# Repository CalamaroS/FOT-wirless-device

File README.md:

# FOT-wirless-device
Master thesis project: Development of a wireless device for lung function assessment in horses.

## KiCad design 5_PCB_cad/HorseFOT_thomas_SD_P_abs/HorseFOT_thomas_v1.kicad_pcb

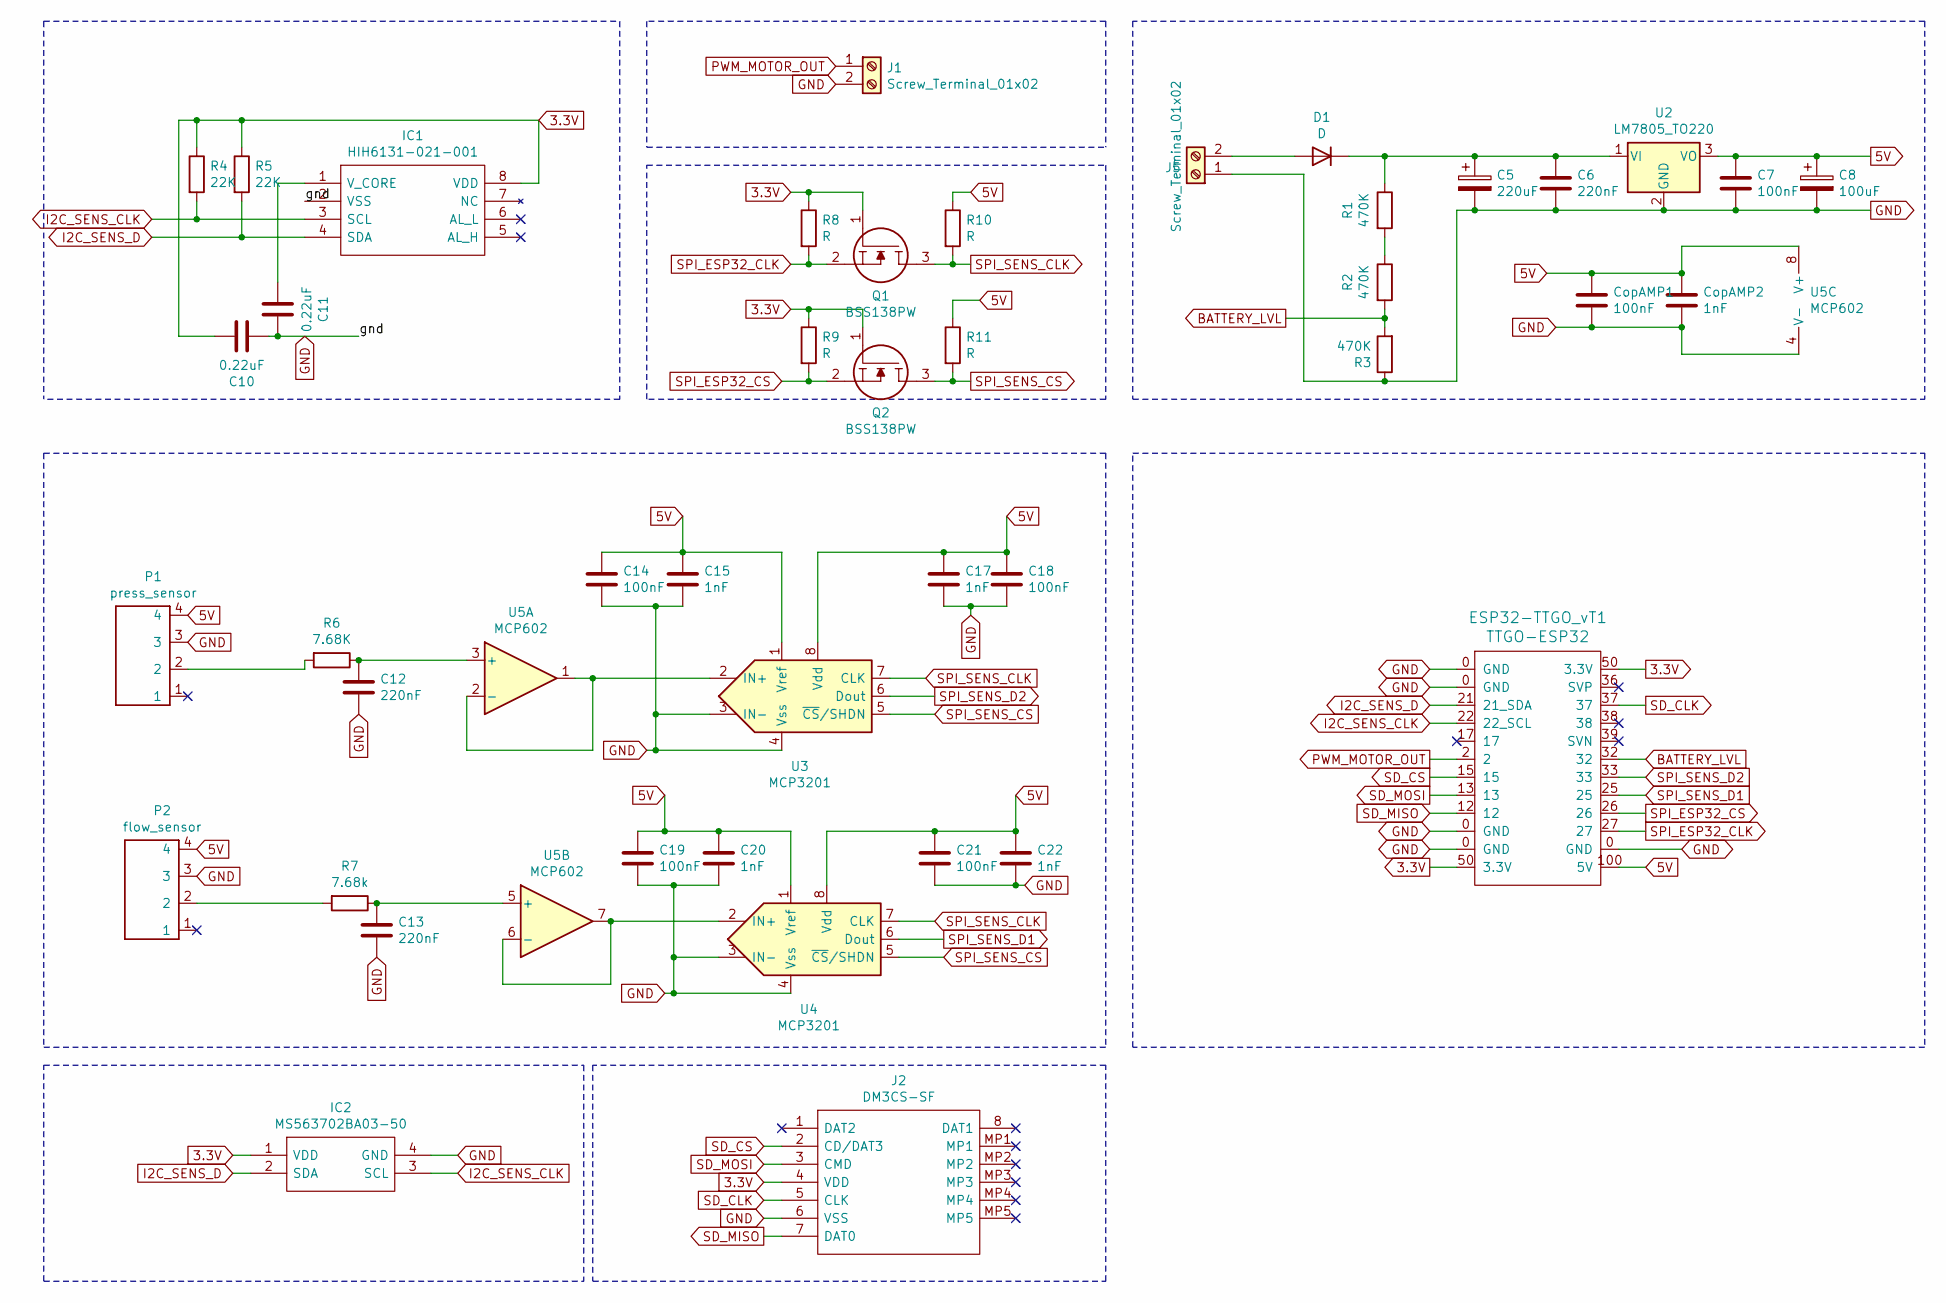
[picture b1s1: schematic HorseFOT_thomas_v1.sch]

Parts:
C5: 220uF; EEE1AA221P
C6, C12, C13: 220nF; C_1206_3216Metric_Pad1.33x1.80mm_HandSolder
C7, C14, C18, C19, C21: 100nF; C_1206_3216Metric_Pad1.33x1.80mm_HandSolder
C8: 100uF; EEE1AA221P
C10, C11: 0.22uF; C_1206_3216Metric_Pad1.33x1.80mm_HandSolder
C15, C17, C20, C22: 1nF; C_1206_3216Metric_Pad1.33x1.80mm_HandSolder
CopAMP1: 100nF; C_1206_3216Metric_Pad1.33x1.80mm_HandSolder
CopAMP2: 1nF; C_1206_3216Metric_Pad1.33x1.80mm_HandSolder
D1: D; D_1206_3216Metric
ESP32-TTGO_vT1: TTGO-ESP32; ESP32-TTGO_vT
IC1: HIH6131-021-001; HIH6131021001; Manufacturer_Part_Number HIH6131-021-001
IC2: MS563702BA03-50; MS5637_1; Manufacturer_Part_Number MS563702BA03-50; Mouser Part Number 824-MS563702BA03-50
J1, J5: Screw_Terminal_01x02; TerminalBlock_bornier-2_P5.08mm
J2: DM3CS-SF; Manufacturer_Part_Number DM3CS-SF; Mouser Part Number 798-DM3CSSF
P1: press_sensor; ELVR-L01D-pressure_sensor
P2: flow_sensor; ELVR-L01D-pressure_sensor
Q1, Q2: BSS138PW; SOT65P210X110-3N; Manufacturer_Part_Number BSS138PW; Mouser Part Number N/A
R1, R2, R3: 470K; R_1206_3216Metric
R4, R5: 22K; R_1206_3216Metric
R6: 7.68K; R_1206_3216Metric
R7: 7.68k; R_1206_3216Metric
R8, R9, R10, R11: R; R_1206_3216Metric_Pad1.30x1.75mm_HandSolder
U2: LM7805_TO220; SOT230P700X180-4N
U3, U4: MCP3201; SOIC127P600X175-8N
U5: MCP602; SOP65P490X110-8N

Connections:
3.3V: C10.1, ESP32-TTGO_vT1.50 (3.3V), IC1.8 (VDD), IC2.1 (VDD), J2.4 (VDD), Q1.1, Q2.1, R4.1, R5.1, R8.1, R9.1
5V: C7.1, C8.1, C14.1, C15.1, C17.1, C18.1, C19.1, C20.1, C21.1, C22.1, CopAMP1.1, CopAMP2.1, ESP32-TTGO_vT1.100 (5V), P1.4, P2.4, R10.1, R11.1, U2.3 (VO), U3.1 (Vref), U3.8 (Vdd), U4.1 (Vref), U4.8 (Vdd), U5.8 (V+)
BATTERY_LVL: ESP32-TTGO_vT1.32, R2.2, R3.2
GND: C5.2, C6.2, C7.2, C8.2, C10.2, C11.1, C12.2, C13.2, C14.2, C15.2, C17.2, C18.2, C19.2, C20.2, C21.2, C22.2, CopAMP1.2, CopAMP2.2, ESP32-TTGO_vT1.0 (GND), IC1.2 (VSS), IC2.4 (GND), J1.2, J2.6 (VSS), J5.1, P1.3, P2.3, R3.1, U2.2 (GND), U3.3 (IN-), U3.4 (Vss), U4.3 (IN-), U4.4 (Vss), U5.4 (V-)
I2C_SENS_CLK: ESP32-TTGO_vT1.22 (22_SCL), IC1.3 (SCL), IC2.3 (SCL), R4.2
I2C_SENS_D: ESP32-TTGO_vT1.21 (21_SDA), IC1.4 (SDA), IC2.2 (SDA), R5.2
unnamed: C5.1, C6.1, D1.1 (K), R1.1, U2.1 (VI)
unnamed: C11.2, IC1.1 (V_CORE)
unnamed: C12.1, R6.1, U5.3 (+)
unnamed: C13.1, R7.1, U5.5 (+)
unnamed: D1.2 (A), J5.2
unnamed: P1.2, R6.2
unnamed: P2.2, R7.2
unnamed: R1.2, R2.1
unnamed: U3.2 (IN+), U5.1, U5.2 (-)
unnamed: U4.2 (IN+), U5.6 (-), U5.7
PWM_MOTOR_OUT: ESP32-TTGO_vT1.2, J1.1
SD_CLK: ESP32-TTGO_vT1.37, J2.5 (CLK)
SD_CS: ESP32-TTGO_vT1.15, J2.2 (CD/DAT3)
SD_MISO: ESP32-TTGO_vT1.12, J2.7 (DAT0)
SD_MOSI: ESP32-TTGO_vT1.13, J2.3 (CMD)
SPI_ESP32_CLK: ESP32-TTGO_vT1.27, Q1.2, R8.2
SPI_ESP32_CS: ESP32-TTGO_vT1.26, Q2.2, R9.2
SPI_SENS_CLK: Q1.3, R10.2, U3.7 (CLK), U4.7 (CLK)
SPI_SENS_CS: Q2.3, R11.2, U3.5 (~CS~/SHDN), U4.5 (~CS~/SHDN)
SPI_SENS_D1: ESP32-TTGO_vT1.25, U4.6 (Dout)
SPI_SENS_D2: ESP32-TTGO_vT1.33, U3.6 (Dout)

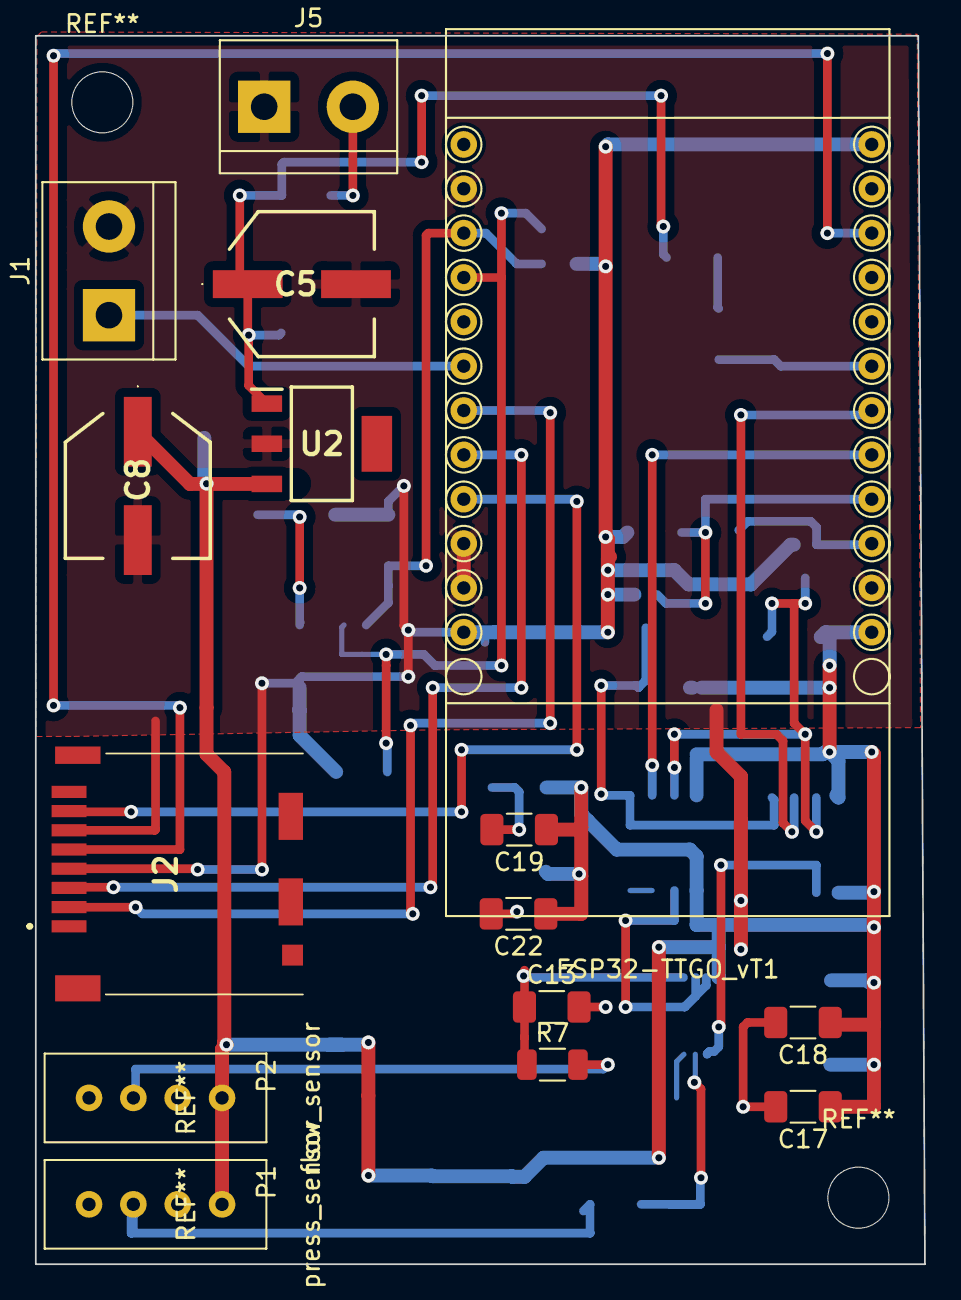
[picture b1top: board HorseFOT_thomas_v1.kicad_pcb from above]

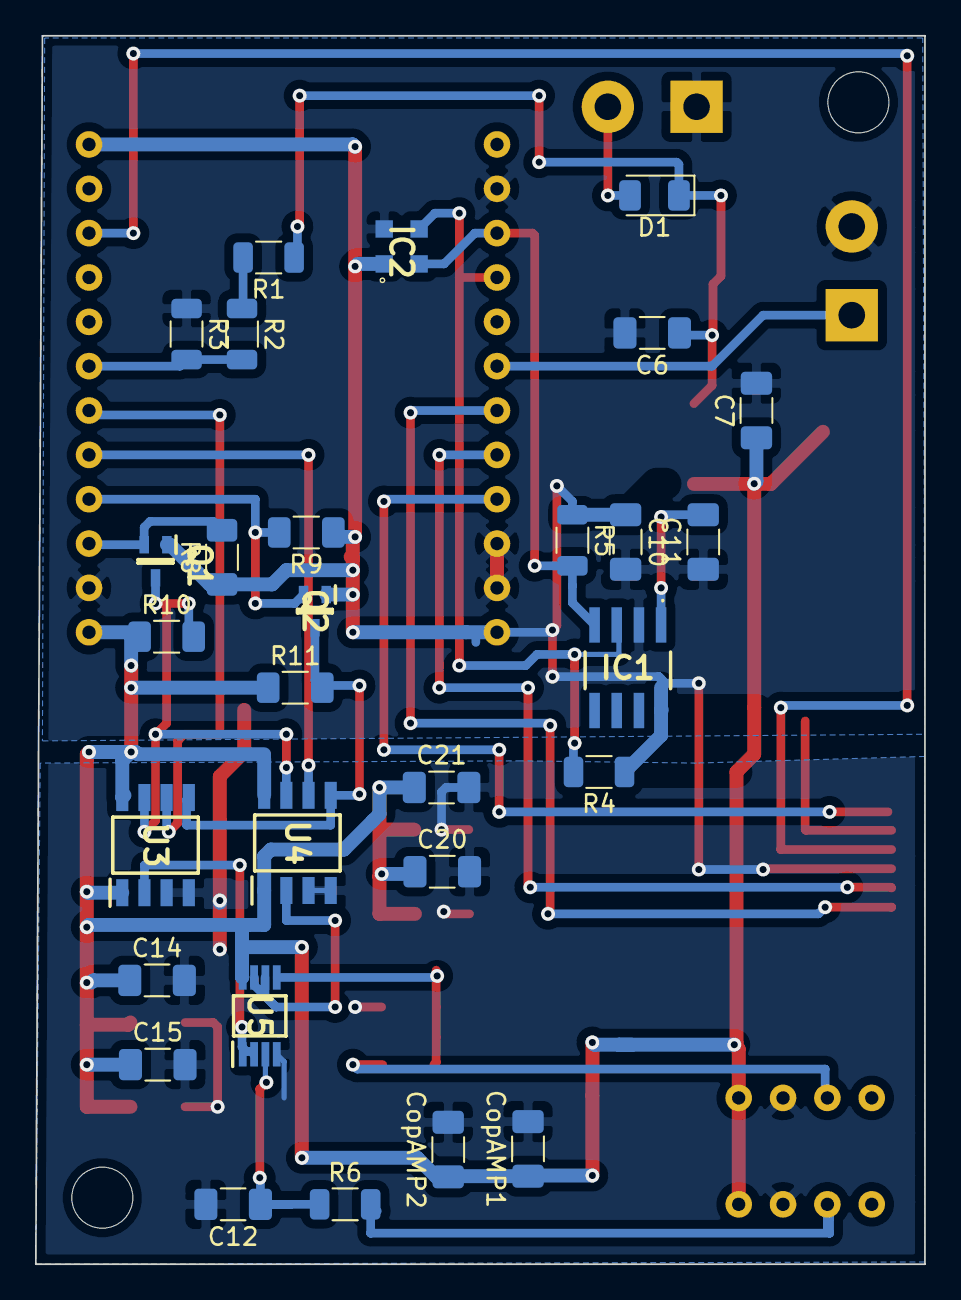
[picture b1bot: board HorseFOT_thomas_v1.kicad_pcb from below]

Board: 2 copper layers, 50.9 x 70.4 mm, 44 parts (29 on the bottom side), 27 nets.

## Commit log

2024-09-25 upload thesis project
